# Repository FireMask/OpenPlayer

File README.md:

# OpenPlayer

Reproductor musical DIY modular basado en Raspberry Pi Zero 2 W, Raspberry Pi OS Lite, MPD, un servicio de control en C#/.NET y un agente de hardware en Python.

## Estado del proyecto

Este repositorio contiene la documentación base para que una persona o un LLM pueda implementar el sistema de forma incremental. Las decisiones que requieren validación física están marcadas como **POR VALIDAR**; no deben asumirse como hardware ya probado.

## Objetivo de la primera versión

- Reproducir archivos locales MP3 y FLAC mediante MPD.
- Utilizar el DAC USB existente con salida de auriculares de 3.5 mm.
- Controlar reproducción, navegación y volumen mediante botones GPIO.
- Controlar y diagnosticar el sistema por SSH.
- Mantener separadas las responsabilidades del servicio C# y del agente Python.
- Pantalla redonda GC9A01 opcional con la pista actual (SPEC 17).
- Preparar soporte futuro para salida Bluetooth A2DP y alimentación portátil.

## Documentación de diseño

- [`docs/architecture.md`](docs/architecture.md): arquitectura, contratos, IPC, software, estados y plan de implementación.
- [`docs/gpio-map.md`](docs/gpio-map.md): asignación GPIO, cableado, seguridad eléctrica y pruebas.
- [`docs/battery-design.md`](docs/battery-design.md): requisitos y opciones para la alimentación portátil.
- [`docs/assembly.md`](docs/assembly.md): montaje, instalación, despliegue, pruebas y solución de problemas. Para cargar música desde Windows, ver §5 "Importar música por Samba" (`\\mpi3-player.local\music`).

> Nota sobre el nombre: el archivo se llama `battery-design.md` (ortografía corregida de `battery-desing.md`).

## Reglas de desarrollo

1. No acoplar el Core a MPD, GPIO, Linux, sockets ni bibliotecas de terceros.
2. MPD es la fuente de verdad para el estado de reproducción.
3. Python detecta entradas físicas y envía eventos; no ejecuta comandos MPD.
4. C# valida los eventos y decide las acciones.
5. No asumir que el DAC es siempre `card 1`; descubrir dispositivos con ALSA.
6. No conectar GPIO a 5 V. Los GPIO de Raspberry Pi son de 3.3 V.
7. No implementar alimentación con batería Li-ion/LiPo sin verificar carga, protección, regulación y apagado seguro.
8. No exponer MPD ni el socket IPC a Internet.
9. Añadir pruebas y actualizar los documentos cuando cambien interfaces o cableado.

## Compilar y probar

Requiere el SDK de .NET 10 (fijado en `global.json`). Las pruebas corren en Windows o Linux:

```bash
dotnet build OpenPlayer.slnx
dotnet test OpenPlayer.slnx
```

## Ejecutar el Service

En la Pi corre como unidad systemd `openplayer` (usuario de sistema `openplayer`, binario en `/opt/openplayer`). Lee `/opt/openplayer/player.json` (copia de `config/player.example.json`) y escucha en el socket Unix `ipc.unixSocketPath` (por defecto `/run/openplayer/hardware.sock`, directorio creado por systemd) mensajes JSON Lines; contrato en [`docs/architecture.md`](docs/architecture.md) §7.

```bash
systemctl status openplayer              # estado
sudo systemctl restart openplayer        # p. ej. tras editar /opt/openplayer/player.json
sudo systemctl stop openplayer
journalctl -u openplayer -b -f           # logs
```

Probar con `socat` (`sudo apt install socat`). El usuario que despliega está en el grupo `openplayer`; tras el primer deploy, abrir una sesión SSH nueva para que el grupo aplique.

```bash
S=UNIX-CONNECT:/run/openplayer/hardware.sock
echo '{"type":"player.get_snapshot"}' | socat - $S
echo '{"type":"button.pressed","button":"play_pause"}' | socat - $S
```

| Mensaje | Efecto |
|---|---|
| `{"type":"button.pressed","button":"<nombre>"}` con `play_pause`, `previous`, `next`, `volume_up`, `volume_down`, `menu`, `seek_forward`, `seek_backward`, `power_off` | Igual que el botón físico (los tres últimos son sus pulsaciones largas; `power_off` apaga la Pi); sin respuesta |
| `{"type":"player.get_snapshot"}` | Responde una línea `player.snapshot`, o `error` si MPD no responde |

Un mensaje inválido o sin MPD accesible solo registra un warning; el proceso sigue. Si `socat` corta la respuesta, usar `socat -t 2`.

Para ejecutarlo a mano (depurar), detener antes la unidad: dos instancias compiten por el socket. Al detenerse, systemd borra `/run/openplayer`, así que hay que recrearlo. Ctrl+C sale con código 0 y borra el socket.

```bash
sudo systemctl stop openplayer
sudo install -d -o openplayer -g openplayer -m 0770 /run/openplayer
sudo -u openplayer /opt/openplayer/OpenPlayer.Service
sudo systemctl start openplayer
```

En Windows (`dotnet run --project src/OpenPlayer.Service`) hay que apuntar `ipc.unixSocketPath` a una carpeta existente (ruta de máximo 108 caracteres).

## Publicar para la Raspberry Pi

Publicación autocontenida (no requiere instalar .NET en la Pi). Desde Windows, `deploy.ps1` compila, copia y ejecuta `deploy/install.sh` con sudo en la Pi:

```powershell
.\deploy.ps1 -Device openplayer.local -User <usuario> [-Password <contraseña>]
```

`install.sh` es idempotente: verifica `python3-gpiozero` y `python3-lgpio` (no los instala), crea el usuario y grupo `openplayer` si faltan, añade `<usuario>` al grupo, instala en `/opt/openplayer` el Service, `hardware-agent/` y `web-agent/` (sin sobrescribir un `player.json` existente; solo le agrega la sección `web` si falta), instala `deploy/openplayer.service`, `deploy/openplayer-hardware.service` y `deploy/openplayer-web.service`, las habilita y las reinicia. También instala la regla polkit `deploy/50-openplayer-poweroff.rules` en `/etc/polkit-1/rules.d/` (deja al usuario `openplayer` apagar la Pi; avisa si falta `polkitd`). Termina con error y muestra `journalctl` si alguna unidad no queda lista.

`-Password` sirve para ssh y sudo, pero queda en el historial de PowerShell; sin él, ssh usa tu clave (`ssh-copy-id`) y sudo pide la contraseña en la terminal.

Sin PowerShell, el equivalente manual:

```bash
dotnet publish src/OpenPlayer.Service -c Release -r linux-arm64 --self-contained true -o publish/linux-arm64
tar -czf openplayer.tgz --exclude=__pycache__ --exclude=requirements-dev.txt -C publish/linux-arm64 . -C "$PWD/src" hardware-agent web-agent
scp openplayer.tgz deploy/install.sh deploy/openplayer.service deploy/openplayer-hardware.service deploy/openplayer-web.service deploy/50-openplayer-poweroff.rules <usuario>@openplayer.local:/tmp/
ssh -t <usuario>@openplayer.local 'sudo bash /tmp/install.sh /tmp/openplayer.tgz /tmp/openplayer.service $USER'
```

La instalación anterior en `~/openplayer` (SPEC 02/03) ya no se usa; se puede borrar con `rm -r ~/openplayer`.

## Hardware agent (botones GPIO)

`src/hardware-agent` (Python, stdlib y `gpiozero`; Pillow y `spidev` solo con pantalla) lee los botones de `hardware.buttons` en `player.json` (BCM, pull-up interno, debounce `hardware.debounceSeconds`) y envía `button.pressed` al socket. Corre como unidad `openplayer-hardware`; si el Service no está disponible, descarta la pulsación con un warning y reconecta solo.

Gestos (SPEC 20). Mantenida = apretada al menos `hardware.holdSeconds` (0,6 s por defecto, 0,2–2). Una pulsación larga nunca dispara la corta.

| Botón | Corta | Mantenida |
|---|---|---|
| ⏭ `next` / ⏮ `previous` | Al soltar: siguiente / anterior | Seek +10 s / −10 s (`player.seekStepSeconds`), repetido cada 0,5 s, con aviso `+10 s` / `−10 s`; nunca cambia de pista |
| vol+ / vol− | Al apretar, como siempre | El mismo paso repetido cada 0,25 s |
| ▶︎⏸ `play_pause` | Al soltar: play/pausa | Cuenta "Apagar 3… 2… 1" y a los `hardware.shutdownHoldSeconds` (3 s, 1–10) apaga la Pi ("Apagando…"). Soltar antes cancela y no hace nada |
| `menu` | Al soltar: cicla los modos de pantalla | Abre el menú en pantalla (SPEC 21) |

Los avisos son una píldora abajo en la pantalla, 1,5 s; sin pantalla, los gestos y el apagado funcionan igual.

Menú en pantalla (SPEC 21, solo con pantalla). Raíz: Biblioteca · Listas · Cola · Apagar. Biblioteca navega carpetas; una pista o "▶ Reproducir todo" ofrece Reproducir (reemplaza la cola), Siguiente y Agregar a la cola. Listas reproduce una lista entera o desde una pista; Cola salta a una pista (♪ = la actual); Apagar pide confirmación (No por defecto). Las listas largas cargan de a 100 solas. Se cierra solo a los 30 s sin botones. Usa la IPC existente: no cambia el Service.

| Botón | Con el menú abierto |
|---|---|
| ⏮ / ⏭ | Subir / bajar (mantenido: rápido, cada 0,15 s); no da vuelta en los extremos |
| ▶︎⏸ | Corta: elegir. Mantenida: apaga igual que afuera |
| `menu` | Corta: volver un nivel (en la raíz, cerrar). Mantenida: cerrar |
| vol± | Volumen, como siempre | Al detenerse, el agente apaga el panel (`DISPOFF`). Tras el apagado el panel sigue alimentado (sin pin BL, la luz queda encendida): cortar con el interruptor de alimentación.

```bash
systemctl status openplayer-hardware
journalctl -u openplayer-hardware -b -f   # connected / disconnected / button <nombre> (sequence N)
```

Sin botones cableados se prueba con un cable dupont entre el GPIO y GND, siguiendo el procedimiento seguro de [`docs/gpio-map.md`](docs/gpio-map.md) §9. Nunca tocar pines de 3.3 V o 5 V.

Pruebas en Windows o Linux (GPIO simulado con `MockFactory`, socket con un servidor TCP local):

```bash
python -m venv .venv
.venv/Scripts/python -m pip install -r src/hardware-agent/requirements-dev.txt   # Linux: .venv/bin/python
.venv/Scripts/python -m pytest tests/hardware-agent
```

Para correrlo en Windows sin hardware: `GPIOZERO_PIN_FACTORY=mock python src/hardware-agent/main.py config/player.example.json` (sin `AF_UNIX`, solo queda desconectado).

### Pantalla redonda (opcional)

El mismo agente dibuja la pista actual (título, artista, álbum, ícono y anillo de progreso) o un reloj en una pantalla GC9A01 de 1,28" 240x240 por SPI (SPEC 17), con el estado que publica el Service (`player.subscribe`). Viene deshabilitada. Para usarla:

1. Cablear según [`docs/gpio-map.md`](docs/gpio-map.md) §10 (VCC a 3.3 V).
2. Activar SPI (`sudo raspi-config nonint do_spi 0`) e instalar `sudo apt install python3-pil python3-spidev fonts-dejavu-core`.
3. Poner `hardware.display.enabled` en `true` en `/opt/openplayer/player.json` y `sudo systemctl restart openplayer-hardware`.

```bash
journalctl -u openplayer-hardware -b -f   # display ready (spi0.0, 40000000 Hz) / display init failed: … / display: disconnected …
```

Con el Service detenido muestra "Sin conexión"; si la pantalla falla, el log lo dice y los botones siguen. `spiHz` y `rotation` se calibran en `player.json`; montaje y problemas en [`docs/assembly.md`](docs/assembly.md) §11.

Modos (SPEC 18, 19): el botón `menu` cicla entre **pista** (ícono, título, artista, álbum, `1:23 / -2:40`, `3 / 12` y anillo de progreso) , **reloj** (HH:MM de 24 h, fecha como `sáb 24 oct` y el anillo si hay pista) y **carátula** (la imagen del álbum en círculo dentro del anillo, sin texto; la incrustada en el archivo o, si no hay, `cover.jpg`/`.png` de la carpeta; sin carátula, ♪ y el título). El modo lo guarda el Service en memoria y vuelve a pista al reiniciarlo. Además:

- En pausa o detenida durante `idleClockSeconds` (60 por defecto; `null` lo desactiva) muestra el reloj; al reproducir vuelve a la pista.
- Cada cambio de volumen muestra 2 s un anillo azul interior y el número grande.
- Un título que no entra se desplaza mientras suena (pausa de 1 s en cada extremo).
- Ahorro opcional (apagado por defecto): `nightStart`/`nightEnd` (`"HH:MM"`, puede cruzar la medianoche) y `offAfterStoppedMinutes` apagan el panel (`DISPOFF`). Cualquier botón la enciende 10 s y además hace su acción; empezar a reproducir también la enciende.

## Web agent (control desde el navegador)

`src/web-agent` (Python, solo stdlib) sirve una página con los 6 botones y el estado actual en `http://mpi3-player.local:8080` (puerto `web.port` de `player.json`). Cada botón envía el mismo `button.pressed` que el botón físico. Una barra de progreso muestra la posición de la pista (`m:ss / m:ss`) y avanza sola; arrastrarla y soltarla salta a esa posición (`player.seek`). La pestaña **Biblioteca** recorre las carpetas de la música, busca por texto y reproduce una pista; con "+" agrega una pista o una carpeta entera a una lista. La pestaña **Listas** maneja las playlists guardadas de MPD (las mismas que `mpc lsplaylists`): crear, renombrar, borrar, reordenar con ↑/↓, quitar y reproducir. Reproducir una pista o una lista **reemplaza la cola actual** sin aviso. Borrar una lista solo borra su `.m3u`, nunca la música. El panel **Cola** (a la derecha en pantallas anchas; debajo de los controles en el móvil) muestra la cola actual de MPD con el origen de cada canción (la lista o "Biblioteca"), la pista actual resaltada con barras animadas (quietas en pausa) y salta a una pista al tocarla. Cada fila de la cola tiene ↑/↓ para reordenar y ✕ para quitarla; "Limpiar" vacía la cola (pide confirmación y detiene la reproducción). Editar la cola no cambia la lista guardada. En la Biblioteca, "+" abre un menú con "Reproducir siguiente" (después de la actual; varias seguidas quedan en orden inverso), "Agregar a la cola" (al final) y "Agregar a una lista ›"; vale para pistas y carpetas. "Guardar como lista" en el panel guarda la cola como una lista nueva (no sobrescribe una existente). La cola funciona como en Spotify: el Service activa el modo `consume` de MPD, así que cada canción terminada o saltada sale de la cola y la actual queda arriba (también afecta a `mpc`, que usa el mismo MPD). ⏮ en los primeros 3 s vuelve a la canción anterior: el Service recuerda las últimas 50 escuchadas y la pone arriba de la cola (la actual queda segunda); pasados 3 s, o sin historial, reinicia la canción actual. El historial se pierde al reiniciar el Service. El origen de cada canción se recuerda en memoria y se pierde al reiniciar el Service. Solo responde a la red local (rangos privados, `::1`, `fe80::/10`) y no pide contraseña; si el Service no está disponible, la página muestra "Sin conexión con el reproductor" y se recupera sola. La página se actualiza al instante (canción, play/pausa, volumen y cola, también si cambian desde `mpc` u otro navegador): el Service avisa cada cambio de MPD y el web agent lo reenvía por `GET /api/events` (SSE). Si ese stream se corta (móvil en segundo plano, reinicio del Service, más de 8 páginas abiertas), la página vuelve a consultar cada 2 s hasta que el navegador reconecta. Corre como unidad `openplayer-web`; contrato HTTP en [`docs/architecture.md`](docs/architecture.md) §5.

```bash
systemctl status openplayer-web
journalctl -u openplayer-web -b -f   # ready / button <nombre> / seek <N> / warnings
journalctl -u openplayer -b -f       # <request> ok / <request> failed: … (biblioteca, listas y cola)
```

Pruebas (Windows o Linux; HTTP real en puerto aleatorio, socket simulado). Correr cada carpeta por separado: ambos agentes tienen su propio `config.py`.

```bash
.venv/Scripts/python -m pytest tests/web-agent
```

Para correrlo en Windows: `python src/web-agent/main.py config/player.example.json` y abrir `http://localhost:8080` (sin `AF_UNIX`, los botones responden 503).

## Estructura

```text
OpenPlayer/
├── README.md
├── LICENSE
├── .gitignore
├── OpenPlayer.slnx
├── global.json
├── Directory.Build.props
├── deploy.ps1
├── specs/
├── docs/
│   ├── architecture.md
│   ├── gpio-map.md
│   ├── battery-design.md
│   └── assembly.md
├── config/
│   └── player.example.json
├── src/
│   ├── OpenPlayer.Core/
│   │   ├── Models/
│   │   ├── Commands/
│   │   └── Interfaces/
│   ├── OpenPlayer.Mpd/
│   ├── OpenPlayer.Service/
│   ├── hardware-agent/
│   └── web-agent/
├── deploy/
│   ├── openplayer.service
│   ├── openplayer-hardware.service
│   └── openplayer-web.service
└── tests/
    ├── OpenPlayer.Core.Tests/
    ├── OpenPlayer.Mpd.Tests/
    ├── OpenPlayer.Service.Tests/
    ├── hardware-agent/
    └── web-agent/
```

## Convenciones para un LLM que trabaje en el repositorio

Antes de implementar una función, leer `README.md` y los documentos relevantes de `docs/`. Respetar las decisiones de arquitectura, distinguir hechos validados de hipótesis, y no cambiar asignaciones de GPIO ni el protocolo IPC sin actualizar documentación y pruebas. Implementar en etapas pequeñas y explicar comandos que requieran privilegios de administrador.

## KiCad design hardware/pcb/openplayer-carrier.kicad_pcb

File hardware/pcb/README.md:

# OpenPlayer carrier PCB — Rev C

Bridge board (SPEC 22, thin Rev B in SPEC 24, Pi sandwich in SPEC 25): connectors only, no active parts. The Pi Zero 2 W plugs into J1 on the back like a HAT, the GC9A01 module is soldered on the front, and the button board, the FM5324GA charge/boost module, the panel power switch and the POWER key connect by cable. Requirements: `docs/pcb-requirements.md`.

Rev A (display plugged on the front, Pi on a ribbon) and Rev B (single-sided, Pi on a ribbon) are in git history only.

> **Never plug power into the Pi's micro-USB PWR port while it sits on the carrier.** The board feeds the Pi through header pins 2 and 4. Block that port in the enclosure.

## Regenerate

Every KiCad file is generated. Do not edit `.kicad_sch` / `.kicad_pcb` / `.kicad_dru` by hand: change the scripts and rerun.

```powershell
python hardware\pcb\scripts\netlist.py        # self-check against config/player.example.json → OK
python hardware\pcb\scripts\build_sch.py      # → openplayer-carrier.kicad_sch
& "C:\Program Files\KiCad\10.0\bin\python.exe" hardware\pcb\scripts\build_pcb.py   # → .kicad_pcb (placed + routed) + .kicad_dru
.\hardware\common\export-fab.ps1 -Board pcb   # ERC + DRC, then Gerbers, drill, BOM, renders → fabrication/
```

| File | Role |
|---|---|
| `scripts/netlist.py` | Single source of truth: parts, footprints and nets |
| `scripts/build_sch.py` | Writes the schematic (stock KiCad 10 symbols, net labels per pin) |
| `scripts/build_pcb.py` | Outline, placement, Pi / display geometry, silkscreen, keep-outs, routing (grid router), GND pours |
| `../common/pcbgen.py` | Generator code shared with the button board: schematic writer, placement, grid router, GND pour |
| `../common/export-fab.ps1` | Fabrication package for any board (`-Board pcb`); refuses to export on any ERC/DRC finding |

- **Change a pin:** edit `NETS` in `netlist.py`. If it is a GPIO, change `config/player.example.json` too; the self-check fails until both agree.
- **Size:** 65 × 53 mm (`BOARD_W` / `BOARD_H` in `build_pcb.py`). The width is the Pi's. The height is the Pi (30) plus the band above it, which J4 (23.5 mm long) needs on the right edge: the Pi's mounting holes leave only 17 mm of edge between them.
- **Pi pin 1 check:** `build_pcb.py` asserts that every J1 pad lands on the Pi header pin of the same number (official Pi Zero 2 W drawing), and draws the Pi outline and pin 1 on `User.Drawings`.
- `openplayer-carrier.kicad_dru` waives courtyard clearance only between J5 and the display holes H5/H6: they sit 3.5 mm from the header, under the module's own tab.
- Order at JLCPCB with `fabrication/openplayer-carrier-gerbers.zip` (2 layers, 1.6 mm, defaults).

## Layout

Seen from the front (the display side). The Pi sits behind the lower 30 mm, ports flush with the bottom edge.

```
            ↑ J7 PWR_BTN
       ┌─────[J7]──────────────────────┐
 ← J2  │                          J4   │ →
 ← J6  │      C1  C2  TPs         BUT- │ →  button strip (right wall)
       ├ H1 ════════ J1 PI ═══════ H2 ┤  ← Pi top edge (Pi behind, y 23–53)
 ← J3  │          display (front)      │
       │      Ø36, centered at y 26    │
       │ H3     H5 ─[ J5 ]─ H6     H4 │
       └───────────────────────────────┘
         Pi ports ↓: mini-HDMI 12.4, USB OTG 41.4, PWR 54.0 mm from the left
```

| Item | Position (mm, front view, origin top-left) |
|---|---|
| Pi outline (back) | x 0–65, y 23–53 |
| Pi M2.5 holes H1–H4 | (3.5, 26.5), (61.5, 26.5), (3.5, 49.5), (61.5, 49.5): 58 × 23 |
| J1 pin 1 | (8.37, 27.77): left end, inner row; pin 2 on the edge row above it |
| J5 pin row | y = 51, pin 1 (VCC, square) rightmost at x = 40.12 |
| Display M2 holes H5/H6 | (22.9, 47.5), (42.1, 47.5): 19.2 c-c, 3.5 mm above the pin row |
| Screen center | (32.5, 26) |
| Antenna keep-out | x 18–37, y 46–53: no copper pour on either layer (pads and tracks may cross) |

## Stack

Front to back, inside a ≈ 80 × 110 × 33 mm portrait case:

| Layer | mm |
|---|---:|
| Display module (4) on its header spacer (2.5) | 6.5 |
| Carrier | 1.6 |
| Gap: J1 socket (8.5) + Pi header plastic (2.5); 11 mm M2.5 standoffs on H1–H4 | 11 |
| Pi Zero 2 W, component side toward the carrier | ~2.2 |
| Gap / insulating sheet | 1 |
| 4000 mAh LiPo, 6 × 60 × 91.5 | 6 |
| **Total** | **~28.3** |

- The display's header is soldered on the back; trim its pins to ≤ 2 mm.
- The J1, C1, C2, TP and XH leads that come through the front sit under the display (2.5 mm gap): trim them flush.
- H5/H6 take 2.5 mm M2 standoffs under the module's tab; the screws go in from the back.

## Connectors and heights

Every cable connector is on the back, mouth at the edge. Pin 1 is marked on the silkscreen. J4 pin names are printed on the front, right of the display; J5 pin names on the back, by the solder joints.

Height rule: part height + Pi part under it ≤ 10.5 mm (the 11 mm gap minus 0.5 mm air). Part heights are from KiCad's 3D models; Pi part heights are typical datasheet values (mini-HDMI ≈ 3.2, micro-USB ≈ 2.7, microSD / CSI / SoC ≤ 1.5): measure at bring-up.

| Ref | Name | Part | Edge, wire direction | Height | Pi part under it | Sum | Pins |
|---|---|---|---|---:|---|---:|---|
| J1 | PI | 2×20 female socket, 2.54 mm, vertical, 8.5 mm (`PinSocket_2x20_P2.54mm_Vertical`) | — (Pi plugs in) | 8.5 | header plastic 2.5 | 11 (the gap) | J1 pin N = Pi pin N |
| J2 | PWR_IN | JST-XH 2 side entry, S2B-XH-A | left, top | 6.1 | none (above the Pi) | 6.1 | 1 5V (module `5V +`), 2 GND (module `−`) |
| J6 | SWITCH | JST-XH 2 side entry, S2B-XH-A, to a ≥ 3 A panel switch | left, top | 6.1 | none | 6.1 | 1 5V_IN, 2 5V_SYS |
| J3 | KEY | JST-XH 2 side entry, S2B-XH-A | left, middle | 6.1 | microSD ≈ 1.3 | 7.4 | 1 PWR_KEY (module `K`), 2 GND |
| J4 | BUTTONS | JST-XH 8 side entry, S8B-XH-A | right, top | 6.1 | none | 6.1 | 1 GND, 2 PLAY (GPIO17), 3 PREV (GPIO27), 4 NEXT (GPIO22), 5 VOL+ (GPIO23), 6 VOL− (GPIO24), 7 MENU (GPIO25), 8 PWR_KEY |
| J7 | PWR_BTN | JST-XH 2 side entry, S2B-XH-A, to a panel momentary key | top, up | 6.1 | none | 6.1 | 1 PWR_KEY, 2 GND |
| J5 | DISPLAY | holes for the module's pre-soldered 1×7 2.54 mm header (`PinHeader_1x07_P2.54mm_Vertical`); nothing to buy | — | pins ≤ 2 (trimmed) | micro-USB OTG ≈ 2.7 | 4.7 | 1 VCC 3V3, 2 GND, 3 SCL (GPIO11), 4 SDA (GPIO10), 5 DC (GPIO16), 6 CS (GPIO8/CE0), 7 RST (GPIO26) |
| C1 | — | 470 µF / 10 V, Ø8 mm radial, **lying flat** | — | ≈ 8 | none | 8 | optional |
| C2 | — | 100 nF disc, standing | — | ≤ 7.5 | none | 7.5 | — |
| TP1–3 | GND / 5V / 3V3 | THT test pads | — | ~0 | none | ~0 | — |
| H5/H6 | — | M2 screw heads | — | ≈ 1.6 | micro-USB OTG ≈ 2.7 | 4.3 | — |

- C1 and C2 sit above the Pi, never over its ports (they would exceed 10.5 mm there).
- `PWR_KEY` goes to the module's `K` pad (J3), the POWER key (J7) and J4 pin 8. It is not a Pi GPIO. The 6-key button board leaves J4 pin 8 unconnected; the pin stays so the XH-8 cable is unchanged.
- The battery connects straight to the module, never to this board.
- C1 is optional: populate it if the Pi resets when USB-C is plugged in. Bend its leads 90° so the body lies inside the silkscreen outline, with `+` on the marked pad. The outlined area is a keep-out for other parts.
- Test points: TP1 GND, TP2 5V_SYS, TP3 3V3.

## Cables

| Cable | Ends | Wiring |
|---|---|---|
| Buttons | J4 XH-8 → button board J1 XH-8 | Straight, pin 1 → pin 1 (`hardware/buttons/README.md`) |
| POWER key | J7 XH-2 → panel momentary key on the case's top edge | Either way round (key shorts PWR_KEY to GND) |
| Power | J2 / J3 → module `5V +` `−` / `K`; J6 → panel switch | XH-2 pigtails, short |

Check every cable pin by pin with a meter before connecting.

## Bring-up

See the checklist in `docs/pcb-requirements.md` §9. Power up first without the Pi, check 5 V at TP2 with the switch on and 0 V with it off. Before plugging the Pi in, check with a meter that J1 pins 2 and 4 carry 5 V and no other J1 pin does, and that the Pi goes on component side toward the carrier, its ports at the bottom edge.

- Measure SoC and battery temperature under load (battery < 45 °C).
- Test Wi-Fi/BT range: the antenna sits between the carrier and the battery.

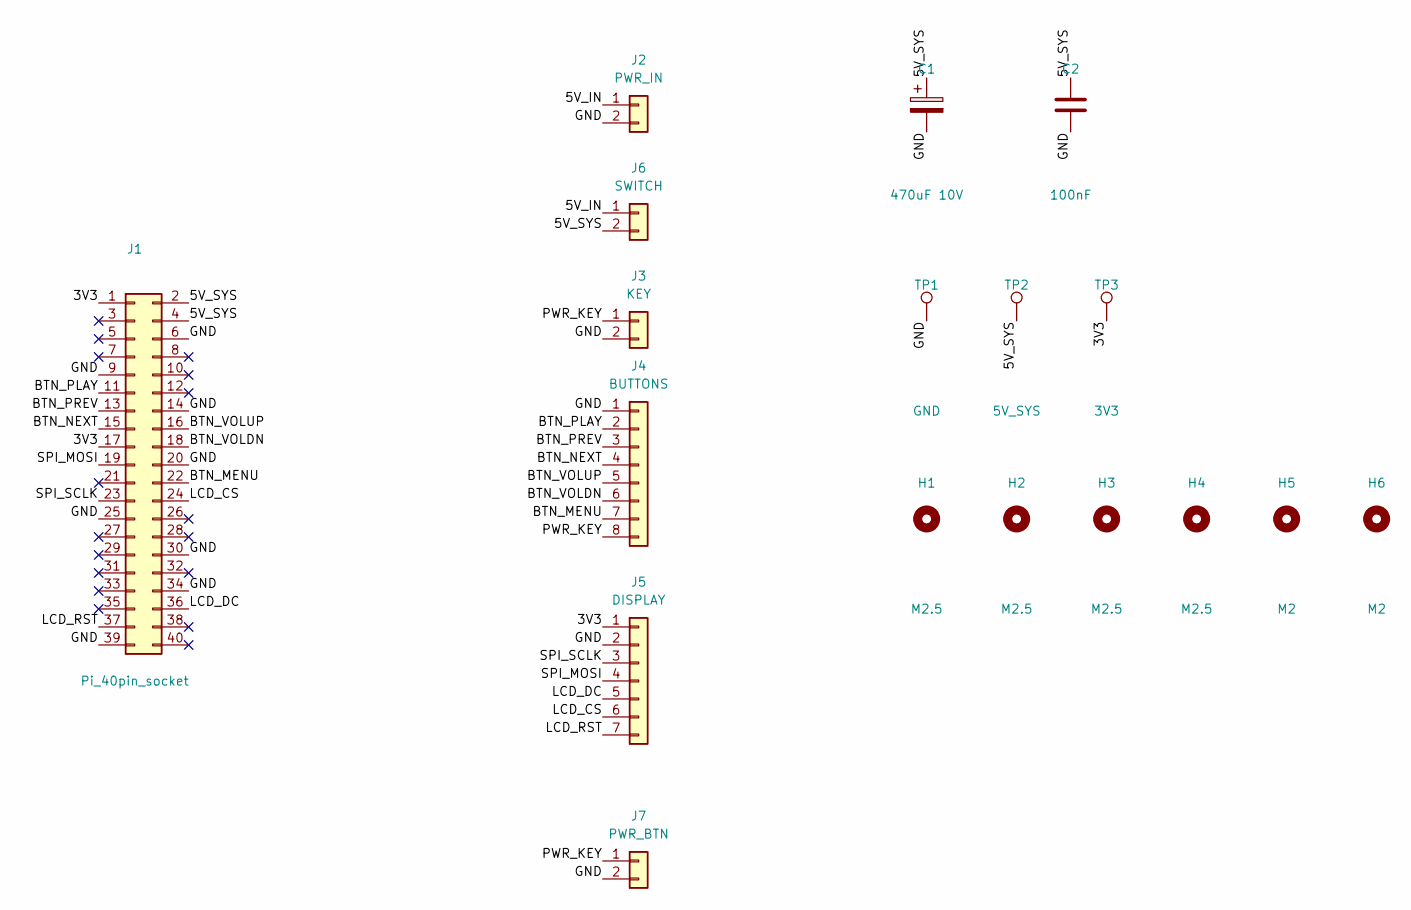
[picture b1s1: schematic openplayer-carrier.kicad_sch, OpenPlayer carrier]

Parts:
C1: 470uF 10V; CP_Radial_D8.0mm_P3.50mm
C2: 100nF; C_Disc_D5.0mm_W2.5mm_P5.00mm
H1, H2, H3, H4: M2.5; MountingHole_2.7mm_M2.5
H5, H6: M2; MountingHole_2.2mm_M2
J1: Pi_40pin_socket; PinSocket_2x20_P2.54mm_Vertical
J2: PWR_IN; JST_XH_S2B-XH-A_1x02_P2.50mm_Horizontal
J3: KEY; JST_XH_S2B-XH-A_1x02_P2.50mm_Horizontal
J4: BUTTONS; JST_XH_S8B-XH-A_1x08_P2.50mm_Horizontal
J5: DISPLAY; PinHeader_1x07_P2.54mm_Vertical
J6: SWITCH; JST_XH_S2B-XH-A_1x02_P2.50mm_Horizontal
J7: PWR_BTN; JST_XH_S2B-XH-A_1x02_P2.50mm_Horizontal
TP1: GND; TestPoint_THTPad_D2.0mm_Drill1.0mm
TP2: 5V_SYS; TestPoint_THTPad_D2.0mm_Drill1.0mm
TP3: 3V3; TestPoint_THTPad_D2.0mm_Drill1.0mm

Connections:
/3V3: J1.1, J1.17, J5.1, TP3.1
/5V_IN: J2.1, J6.1
/5V_SYS: C1.1, C2.1, J1.2, J1.4, J6.2, TP2.1
/BTN_MENU: J1.22, J4.7
/BTN_NEXT: J1.15, J4.4
/BTN_PLAY: J1.11, J4.2
/BTN_PREV: J1.13, J4.3
/BTN_VOLDN: J1.18, J4.6
/BTN_VOLUP: J1.16, J4.5
/GND: C1.2, C2.2, J1.6, J1.9, J1.14, J1.20, J1.25, J1.30, J1.34, J1.39, J2.2, J3.2, J4.1, J5.2, J7.2, TP1.1
/LCD_CS: J1.24, J5.6
/LCD_DC: J1.36, J5.5
/LCD_RST: J1.37, J5.7
/PWR_KEY: J3.1, J4.8, J7.1
/SPI_MOSI: J1.19, J5.4
/SPI_SCLK: J1.23, J5.3

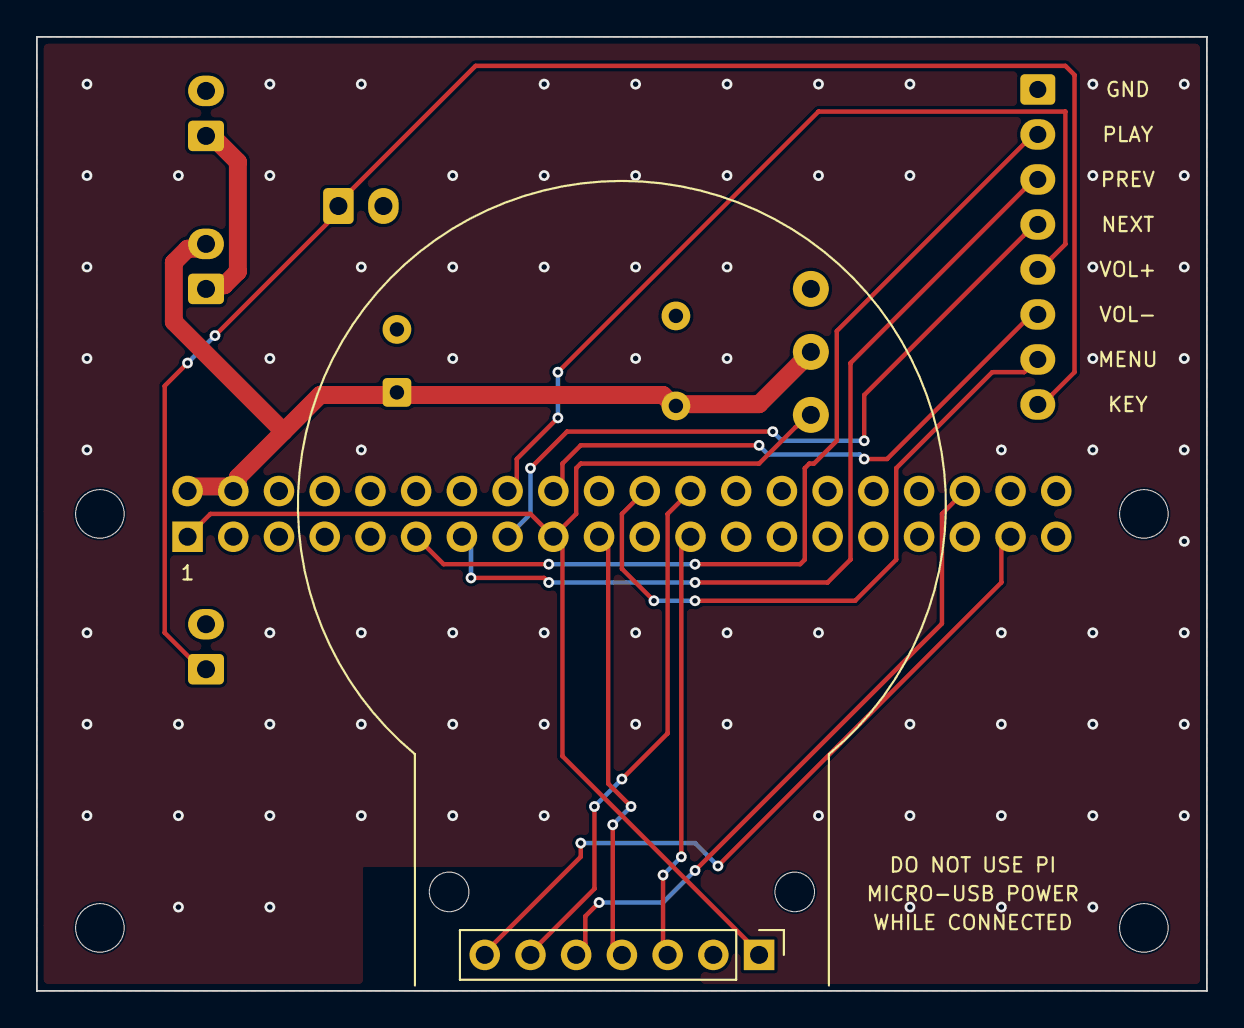
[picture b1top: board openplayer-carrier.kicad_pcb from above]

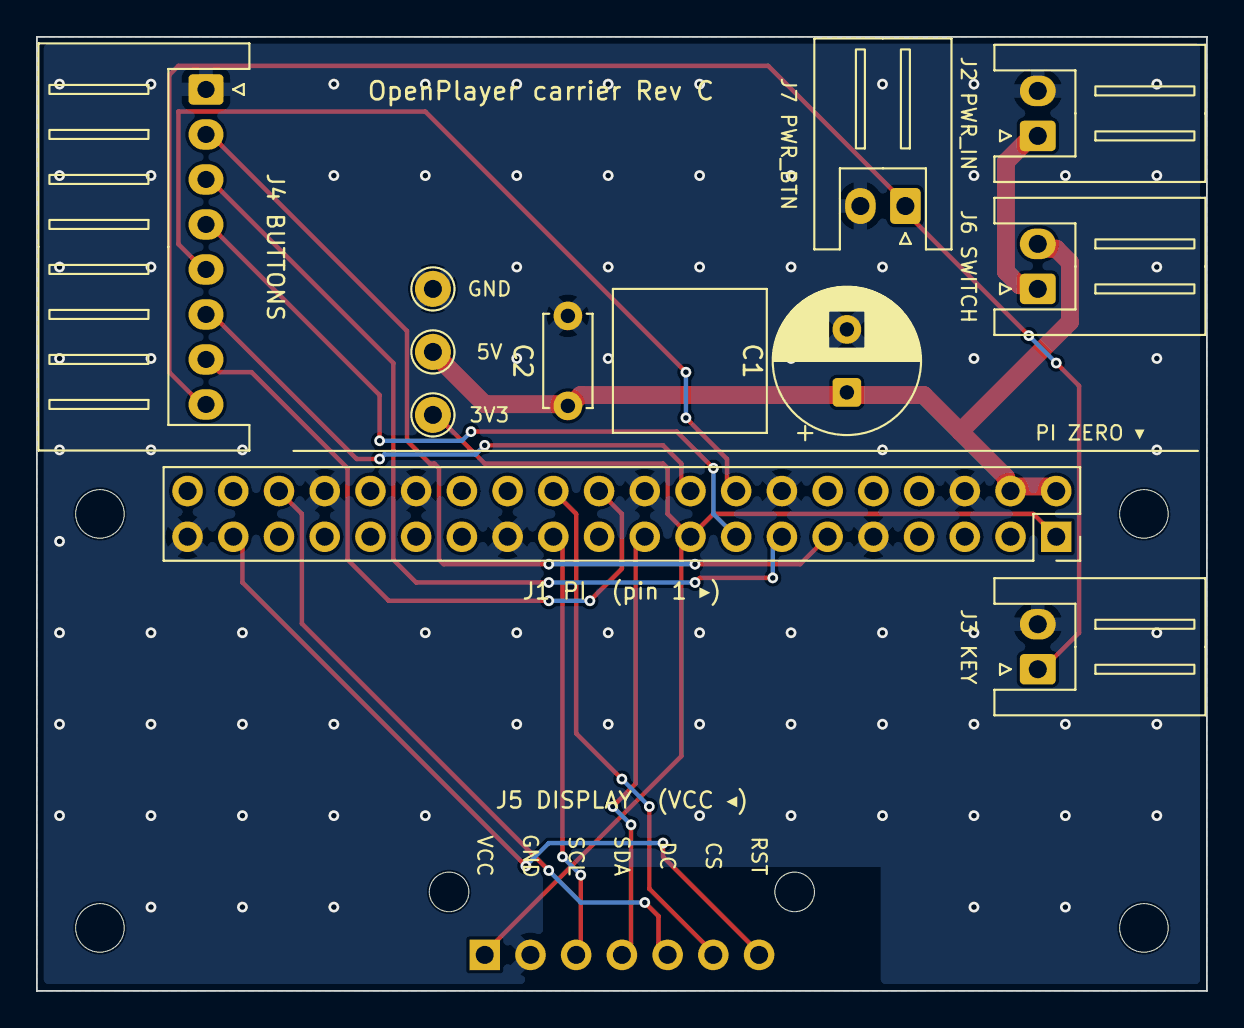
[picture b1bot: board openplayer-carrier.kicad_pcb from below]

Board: 2 copper layers, 65.0 x 53.0 mm, 18 parts (11 on the bottom side), 16 nets.

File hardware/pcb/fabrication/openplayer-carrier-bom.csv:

"Refs","Value","Footprint","Description","Qty"
"C1","470uF 10V","Capacitor_THT:CP_Radial_D8.0mm_P3.50mm","","1"
"C2","100nF","Capacitor_THT:C_Disc_D5.0mm_W2.5mm_P5.00mm","","1"
"J1","Pi_40pin_socket","Connector_PinSocket_2.54mm:PinSocket_2x20_P2.54mm_Vertical","","1"
"J2","PWR_IN","Connector_JST:JST_XH_S2B-XH-A_1x02_P2.50mm_Horizontal","","1"
"J3","KEY","Connector_JST:JST_XH_S2B-XH-A_1x02_P2.50mm_Horizontal","","1"
"J4","BUTTONS","Connector_JST:JST_XH_S8B-XH-A_1x08_P2.50mm_Horizontal","","1"
"J5","DISPLAY","Connector_PinHeader_2.54mm:PinHeader_1x07_P2.54mm_Vertical","","1"
"J6","SWITCH","Connector_JST:JST_XH_S2B-XH-A_1x02_P2.50mm_Horizontal","","1"
"J7","PWR_BTN","Connector_JST:JST_XH_S2B-XH-A_1x02_P2.50mm_Horizontal","","1"

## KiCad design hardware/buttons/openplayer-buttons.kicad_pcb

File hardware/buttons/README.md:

# OpenPlayer button board — Rev B

Side strip (SPEC 23; 6 keys since SPEC 25): six 6×6 mm tactile switches in one row and an 8-pin JST-XH to the carrier's J4. No active parts. Requirements: `docs/pcb-requirements.md` §4.7. The POWER key moved to the case's top edge, on the carrier's J7; Rev A (7 keys, 116 mm) is in git history only.

## Regenerate

Every KiCad file is generated. Do not edit `.kicad_sch` / `.kicad_pcb` by hand: change the scripts and rerun.

```powershell
python hardware\buttons\scripts\netlist.py        # self-check: J1 pinout = carrier J4 → OK
python hardware\buttons\scripts\build_sch.py      # → openplayer-buttons.kicad_sch
& "C:\Program Files\KiCad\10.0\bin\python.exe" hardware\buttons\scripts\build_pcb.py   # → .kicad_pcb (placed + routed)
.\hardware\common\export-fab.ps1 -Board buttons   # ERC + DRC, then Gerbers, drill, BOM, renders → fabrication/
```

| File | Role |
|---|---|
| `scripts/netlist.py` | Single source of truth: parts, footprints and nets; checks J1 against the carrier |
| `scripts/build_sch.py` | Writes the schematic |
| `scripts/build_pcb.py` | Outline, placement, silkscreen, routing, GND pour; size parameters |
| `../common/pcbgen.py` | Generator code shared with the carrier |
| `../common/export-fab.ps1` | Fabrication package; refuses to export on any ERC/DRC finding |

## Resize

Change the parameters at the top of `scripts/build_pcb.py` and rerun `build_pcb.py`; the length is computed and printed.

| Parameter | Default | Meaning |
|---|---|---|
| `BTN_PITCH` | 9.6 mm | Switch center to center within a group (≥ 9.6, the switch courtyard) |
| `GROUP_GAP` | 4 mm | Extra space between groups, and between J1 and the first switch |
| `GROUPS` | VOL+ VOL− \| PREV PLAY NEXT MENU | Order and grouping, top to bottom |
| `BOARD_W` | 14 mm | Strip width; widen it if routing fails |
| `END_MARGIN` | 5.5 mm | Last switch / connector to board end; the M2 holes sit here |

Default size 14 × 100.09 mm: fits the ≈ 104 mm inside height of the portrait case.

## Parts

| Ref | Part | Side |
|---|---|---|
| SW2–SW7 | 6×6 mm THT tactile (`SW_PUSH_6mm`), VOL+, VOL−, PREV, PLAY, NEXT, MENU top to bottom (no SW1) | Front (toward the side wall) |
| J1 | `CARRIER`, JST-XH 8 (B8B-XH-A), pin 1 at the top | Back, top end |
| H1, H2 | M2 mounting holes, one at each end | — |

Switch height (4.3–13 mm) is chosen when buying, to suit the button holders; every `SW_PUSH_6mm_H*` variant uses the same pads.

## Pinout and cable

J1 has the same pinout as the carrier's J4, so the cable is **XH-8 to XH-8, straight: pin 1 to pin 1** (not reversed).

| J1 pin | Net | Button | Carrier J4 pin |
|---:|---|---|---:|
| 1 | GND | common | 1 |
| 2 | BTN_PLAY | PLAY (SW5) | 2 |
| 3 | BTN_PREV | PREV (SW4) | 3 |
| 4 | BTN_NEXT | NEXT (SW6) | 4 |
| 5 | BTN_VOLUP | VOL+ (SW2) | 5 |
| 6 | BTN_VOLDN | VOL− (SW3) | 6 |
| 7 | BTN_MENU | MENU (SW7) | 7 |
| 8 | — (no-connect, silkscreen `NC`) | — | 8 (PWR_KEY) |

- Each switch shorts its signal to GND. Pull-ups and debounce are on the Pi side (internal pull-ups, `debounceSeconds`).
- Pin 8 stays in the connector so the XH-8 cable is unchanged; the carrier still routes PWR_KEY to it. POWER is a panel key on J7 of the carrier (module `K` pad, not a GPIO). Shut down with a 3 s hold on PLAY.
- Pin 1 is marked on both boards. Check continuity pin by pin before connecting the cable.

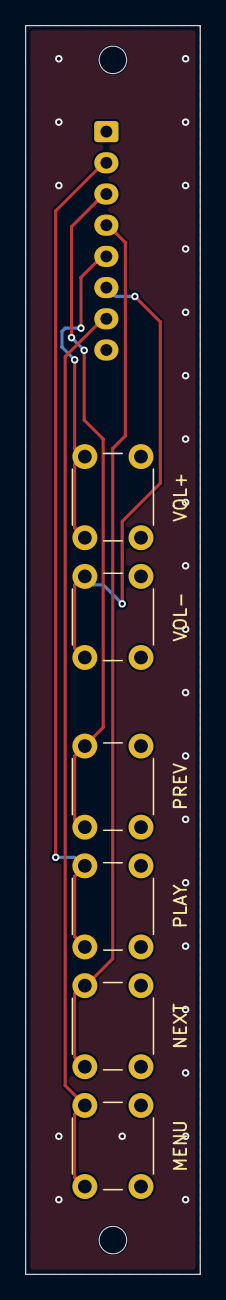
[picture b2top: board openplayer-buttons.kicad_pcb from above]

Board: 2 copper layers, 14.0 x 100.1 mm, 9 parts (1 on the bottom side), 7 nets.

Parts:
H1, H2: M2; MountingHole_2.2mm_M2
J1: CARRIER; JST_XH_B8B-XH-A_1x08_P2.50mm_Vertical
SW2: VOL+; SW_PUSH_6mm
SW3: VOL-; SW_PUSH_6mm
SW4: PREV; SW_PUSH_6mm
SW5: PLAY; SW_PUSH_6mm
SW6: NEXT; SW_PUSH_6mm
SW7: MENU; SW_PUSH_6mm

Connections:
/BTN_MENU: J1.7, SW7.1
/BTN_NEXT: J1.4, SW6.1
/BTN_PLAY: J1.2, SW5.1
/BTN_PREV: J1.3, SW4.1
/BTN_VOLDN: J1.6, SW3.1
/BTN_VOLUP: J1.5, SW2.1
/GND: J1.1, SW2.2, SW3.2, SW4.2, SW5.2, SW6.2, SW7.2

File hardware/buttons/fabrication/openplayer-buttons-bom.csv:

"Refs","Value","Footprint","Description","Qty"
"J1","CARRIER","Connector_JST:JST_XH_B8B-XH-A_1x08_P2.50mm_Vertical","","1"
"SW1","POWER","Button_Switch_THT:SW_PUSH_6mm","6x6 THT tactile, height per enclosure","1"
"SW2","VOL+","Button_Switch_THT:SW_PUSH_6mm","6x6 THT tactile, height per enclosure","1"
"SW3","VOL-","Button_Switch_THT:SW_PUSH_6mm","6x6 THT tactile, height per enclosure","1"
"SW4","PREV","Button_Switch_THT:SW_PUSH_6mm","6x6 THT tactile, height per enclosure","1"
"SW5","PLAY","Button_Switch_THT:SW_PUSH_6mm","6x6 THT tactile, height per enclosure","1"
"SW6","NEXT","Button_Switch_THT:SW_PUSH_6mm","6x6 THT tactile, height per enclosure","1"
"SW7","MENU","Button_Switch_THT:SW_PUSH_6mm","6x6 THT tactile, height per enclosure","1"
